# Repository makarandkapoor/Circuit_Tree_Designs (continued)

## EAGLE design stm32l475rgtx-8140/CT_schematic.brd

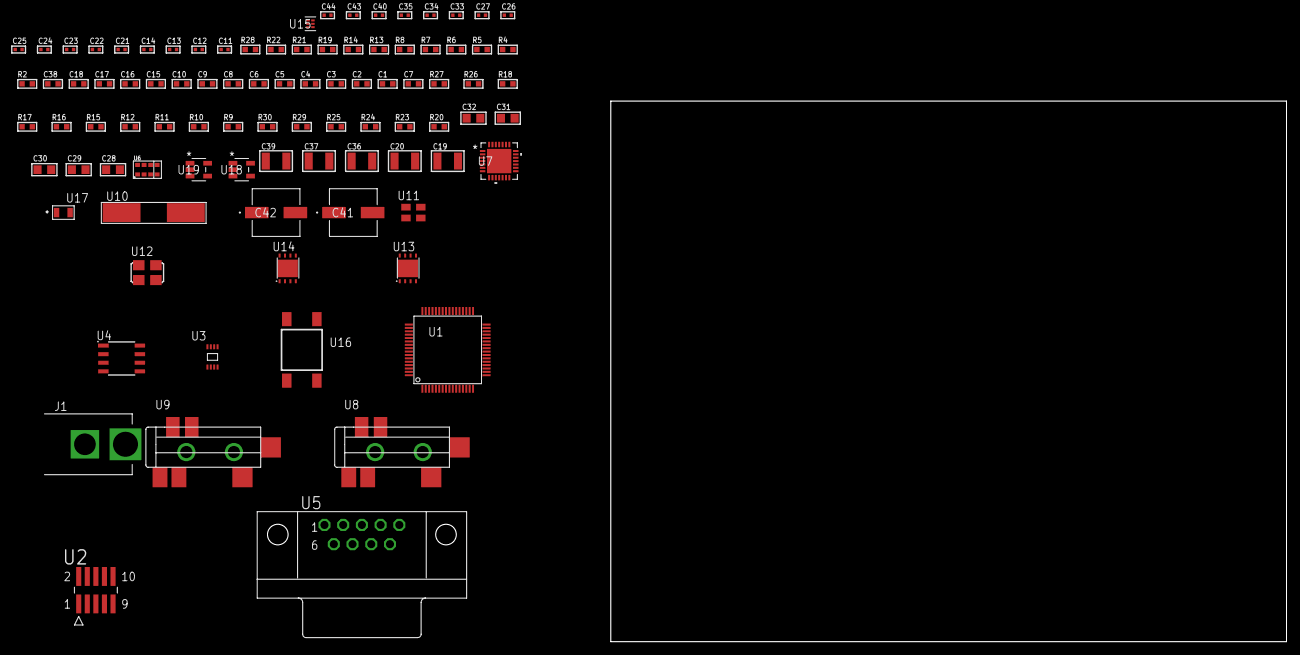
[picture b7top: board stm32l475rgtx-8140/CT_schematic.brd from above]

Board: 2 copper layers, 100.0 x 80.0 mm, 92 parts (0 on the bottom side), 42 nets, no tracks yet.

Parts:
C1, C10, C15, C16, C17, C18: 1e-06; C0603
C2, C3, C4, C5, C6, C8: 1e-07; C0603
C7: 4.7e-06; C0603
C9: 1e-08; C0603
C11, C12: 1e-11; C0402
C13, C23, C24, C25, C26, C27, C40: 1e-07; C0402
C14, C33, C34, C35, C43, C44: 1e-08; C0402
C19, C20: 2.2e-05; C1210
C21, C22: 1e-09; C0402
C28, C29, C30, C31, C32: 1e-05; C0805
C36, C37, C39: 1e-05; C1210
C38: 8e-07; R0603
C41, C42: 0.0001; EXV-9H
J1: PJ-037B; PJ-037B_PACKAGE
R2, R22: 1000.0; R0603
R4: 4700.0; R0603
R5, R6, R7, R8: 2200.0; R0603
R9, R10, R11, R12, R15, R26, R27: 10000.0; R0603
R13: 5.0; R0603
R14: 120.0; R0603
R16, R17, R18: 47000.0; R0603
R19: 680.0; R0603
R20, R23, R25: 100000.0; R0603
R21: 2231.0; R0603
R24: 300000.0; R0603
R28: 9100.0; R0603
R29: 680000.0; R0603
R30: 120000.0; R0603
U1: STM32L475RGT6; LQFP64
U2: FTSH-105-01-L-DV-K; SAMTEC_FTSH-105-01-L-DV-K
U3: 24AA16-I/MC; TDFN-8/6MM
U4: MCP2562-E/SN; SOIC-8
U5: 182-009-113R531; 182-009-MALE
U6: TMD27711; SMD-8
U7: WM8731CLSEFL; QFN-28
U8, U9: SJ-43515TS-SMT-TR
U10: ABLS-25.000MHZ-B2F-T
U11: ASEK-32.768KHz-ECST; ASEK
U12: ASFL1-12.288MHZ-EC-T; ASFL1
U13: LP3878SDX-ADJ/NOPB; WSON-8
U14: LP2951ACSDX/NOPB; WSON-8
U15: TPS3895ADRYR; SON-6
U16: 4-1437565-2; SW_4-1437565-2
U17: Q65110A2395; LGM67K-G1J2-24-Z
U18, U19: nc7sz125m5x; NC7SZ125M5X

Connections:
CLK_CRYSTAL_U1_5: C11.1, U1.5, U10.1
CLK_CRYSTAL_U1_6: C12.1, U1.6, U10.2
CLK_U1_3: U1.3, U11.3
CLK_U7_1: U7.1, U12.3
GND: C1.2, C2.2, C3.2, C4.2, C5.2, C6.2, C7.2, C8.2, C9.2, C10.2, C11.2, C12.2, C13.2, C14.2, C15.2, C16.2, C17.2, C18.2, C22.2, C23.2, C24.2, C25.2, C26.2, C27.2, C28.2, C29.2, C30.2, C31.2, C32.2, C33.2, C34.2, C35.2, C36.2, C37.2, C38.2, C39.2, C40.2, C41.2, C42.2, C43.2, C44.2, J1.2, R2.2, R9.2, R13.2, R16.2, R17.2, R18.2, R22.2, R25.2, R28.2, R30.2, U1.12, U1.18, U1.31, U1.47, U1.63, U2.3, U2.5, U3.4, U3.7, U4.2, U4.8, U5.5, U6.3, U7.4, U7.15, U7.19, U7.25, U7.26, U7.29, U8.1, U9.1, U11.2, U12.2, U13.3, U13.PAD, U14.3, U14.4, U14.PAD, U15.2, U17.C, U18.2, U18.3, U19.1, U19.3
NET_U1_7: R4.1, U1.7, U19.4
NET_U1_30: R8.1, U1.30, U3.5
NET_U1_34: R7.1, U1.34, U3.6
NET_U1_58: R5.1, U1.58, U6.2
NET_U1_59: R6.1, U1.59, U6.8
NET_U1_60: R9.1, U1.60
NET_U1_61: U16.3, U16.4
NET_U2_9: R13.1, U2.9
NET_U4_6: R14.2, U4.6
NET_U5_2: R14.2, U4.6, U5.2
NET_U5_3: R14.1, U4.7, U5.3
NET_U6_7: R15.1, U6.7
NET_U7_20: C27.1, C32.1, U7.20
NET_U8_2: C20.1, R17.1, U8.2
NET_U8_5: C19.1, R16.1, U8.5
NET_U9_5: C21.1, C22.1, R18.1, R19.1, U9.5
NET_U13_1: C35.1, U13.1
NET_U13_6: R21.2, R22.1, U13.6
NET_U13_8: R20.1, U13.8
NET_U14_5: R23.1, U14.5
NET_U14_7: R24.2, R25.1, U14.7
NET_U15_1: R27.1, R28.1, U15.1
NET_U15_3: R29.2, R30.1, U15.3
NET_U15_4: R26.1, U15.4, U18.4, U19.2
NET_U16_1: R2.1, U16.1, U16.2
PROC_CAN1_RX: U1.44, U4.4
PROC_CAN1_TX: U1.45, U4.1
PROC_SAI1_FS_A: U1.62, U7.9, U7.11
PROC_SAI1_SCK_A: U1.29, U7.7
PROC_SAI1_SD_A: U1.11, U7.8
PROC_SYS_JTCK_SWCLK: R11.1, U1.49, U2.4
PROC_SYS_JTDO_SWO: U1.55, U2.6
PROC_SYS_JTMS_SWDIO: R12.1, U1.46, U2.2
RST_OUT_U2_JTAG_RST_B: R10.1, U2.10, U18.1
VCC_S1_16V0: C36.1, C38.1, C41.1, C42.1, J1.1, R20.2, U13.4, U14.8
VCC_TIER1_3V3: C1.1, C2.1, C3.1, C4.1, C5.1, C6.1, C7.1, C8.1, C9.1, C10.1, C13.1, C14.1, C16.1, C17.1, C18.1, C23.1, C24.1, C25.1, C26.1, C28.1, C29.1, C30.1, C31.1, C33.1, C34.1, C37.1, C40.1, C43.1, C44.1, R4.2, R5.2, R6.2, R7.2, R8.2, R10.2, R11.2, R12.2, R15.2, R21.1, R26.2, R27.2, R29.1, U1.1, U1.13, U1.19, U1.32, U1.48, U1.64, U2.1, U3.8, U4.5, U6.1, U6.4, U7.3, U7.5, U7.12, U7.18, U11.4, U12.4, U13.5, U15.6, U18.5, U19.5
VCC_TIER1_5V0: C15.1, C39.1, R23.2, R24.1, U4.3, U14.1

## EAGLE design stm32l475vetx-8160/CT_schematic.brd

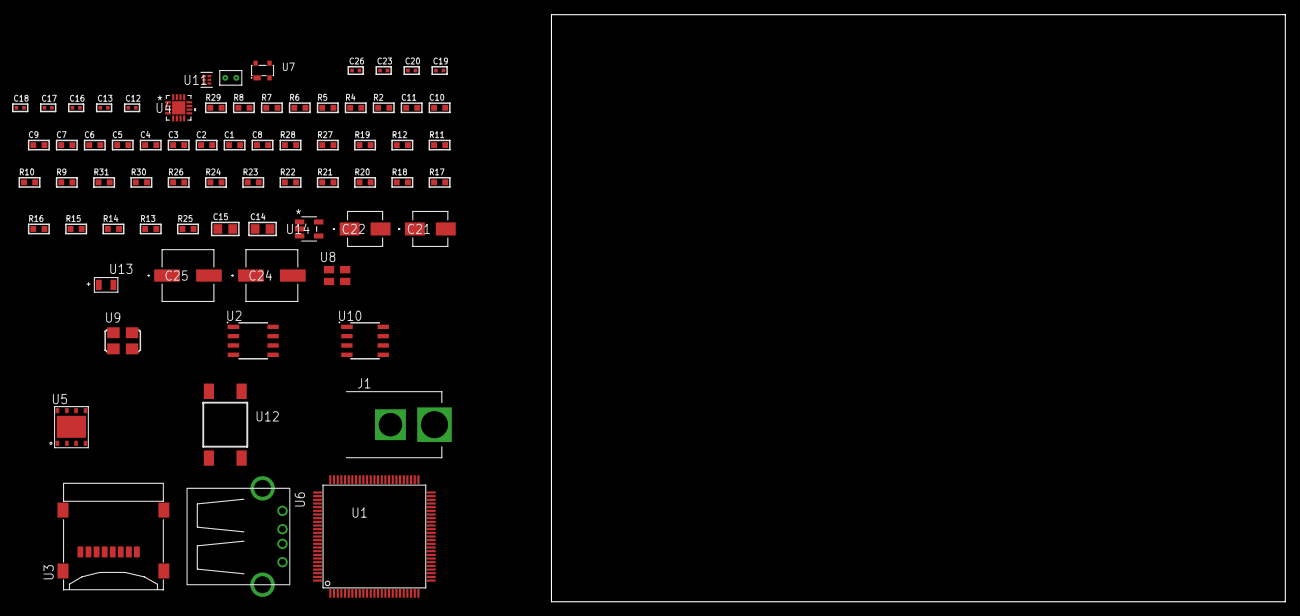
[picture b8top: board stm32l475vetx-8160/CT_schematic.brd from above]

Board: 2 copper layers, 100.0 x 80.0 mm, 71 parts (0 on the bottom side), 41 nets, no tracks yet.

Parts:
C1, C11: 1e-06; C0603
C2, C3, C4, C5, C6, C7, C9: 1e-07; C0603
C8: 4.7e-06; C0603
C10: 1e-08; C0603
C12, C19, C20, C26: 1e-08; C0402
C13, C16, C17, C18, C23: 1e-07; C0402
C14: 1e-05; C0805
C15: 4.7e-06; C0805
C21: 1e-06; EXV-9B
C22: 2.2e-06; EXV-9B
C24, C25: 0.0001; EXV-9H
J1: PJ-037B; PJ-037B_PACKAGE
R2: 1000.0; R0603
R4: 4700.0; R0603
R5, R6, R7, R8: 2200.0; R0603
R9, R10, R11, R12, R19, R27, R28: 10000.0; R0603
R13, R14, R15, R16, R17, R18, R20, R21, R22, R23, R24, R26: 100000.0; R0603
R25: 164658.62; R0603
R29: 9100.0; R0603
R30: 680000.0; R0603
R31: 120000.0; R0603
U1: STM32L475VET6; LQFP100
U2: 24AA1025T-I/SN; SOIC-8
U3: 0472192001; MOLEX_47219-2001
U4: MMA8451QT; QFN-16
U5: SST26VF032B-104I/MF; WFDN-8
U6: 61400416021; USB-A-H
U7: prtr5v0u2ax; SOT143B
U8: ASEK-32.768KHz-ECST; ASEK
U9: ASFL1-25MHZ-NCS; ASFL1
U10: LP2954AIMX/NOPB; LP2954
U11: TPS3895ADRYR; SON-6
U12: 4-1437565-2; SW_4-1437565-2
U13: Q65110A2395; LGM67K-G1J2-24-Z
U14: nc7sz125m5x; NC7SZ125M5X
U15: Dummy; DUMMY_PACKAGE_160

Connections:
CLK_U1_8: U1.8, U8.3
CLK_U1_12: U1.12, U9.3
GND: C1.2, C2.2, C3.2, C4.2, C5.2, C6.2, C7.2, C8.2, C9.2, C10.2, C11.2, C12.2, C13.2, C14.2, C15.2, C16.2, C17.2, C18.2, C19.2, C20.2, C21.2, C22.2, C23.2, C24.2, C25.2, C26.2, J1.2, R2.2, R9.2, R11.2, R19.2, R26.2, R29.2, R31.2, U1.10, U1.19, U1.20, U1.27, U1.49, U1.74, U1.99, U2.4, U2.7, U3.6, U3.G1, U3.G2, U3.G3, U3.G4, U4.5, U4.10, U4.12, U4.17, U5.4, U5.9, U6.4, U6.5, U6.6, U7.1, U8.2, U9.2, U10.4, U11.2, U13.C, U14.1, U14.3, U15.1
NET_U1_14: R4.1, U1.14, U14.4
NET_U1_22: U1.21, U1.22
NET_U1_47: R7.1, U1.47, U2.6
NET_U1_48: R8.1, U1.48, U2.5
NET_U1_92: R5.1, U1.92, U4.4
NET_U1_93: R6.1, U1.93, U4.6
NET_U1_94: R9.1, U1.94
NET_U1_98: U12.3, U12.4
NET_U2_1: R11.1, U2.1
NET_U2_2: R12.1, U2.2
NET_U2_3: R10.1, U2.3
NET_U4_2: C17.1, U4.2
NET_U4_7: R19.1, U4.7
NET_U10_3: R24.1, U10.3
NET_U10_5: R23.1, U10.5
NET_U10_7: R25.2, R26.1, U10.7
NET_U11_1: R28.1, R29.1, U11.1
NET_U11_3: R30.2, R31.1, U11.3
NET_U11_4: R27.1, U11.4, U14.2
NET_U12_1: R2.1, U12.1, U12.2
PROC_DAC1_OUT2: U1.30, U15.2
PROC_QUADSPI_BK1_IO0: U1.36, U5.5
PROC_QUADSPI_BK1_IO1: U1.35, U5.2
PROC_QUADSPI_BK1_IO2: R21.1, U1.32, U5.3
PROC_QUADSPI_BK1_IO3: R22.1, U1.31, U5.7
PROC_QUADSPI_CLK: U1.41, U5.6
PROC_QUADSPI_NCS: R20.1, U1.42, U5.1
PROC_SDMMC1_CK: R14.1, U1.80, U3.5
PROC_SDMMC1_CMD: R13.1, U1.83, U3.3
PROC_SDMMC1_D0: R15.1, U1.65, U3.7
PROC_SDMMC1_D1: R16.1, U1.66, U3.8
PROC_SDMMC1_D2: R17.1, U1.78, U3.1
PROC_SDMMC1_D3: R18.1, U1.79, U3.2
PROC_USB_OTG_FS_DM: U6.2, U7.3
PROC_USB_OTG_FS_DP: U6.3, U7.2
PROC_USB_OTG_FS_VBUS: U6.1, U7.4
VCC_S1_16V8: C21.1, C24.1, C25.1, J1.1, R24.2, U10.8
VCC_TIER1_3V3: C1.1, C2.1, C3.1, C4.1, C5.1, C6.1, C7.1, C8.1, C9.1, C10.1, C11.1, C12.1, C13.1, C14.1, C15.1, C16.1, C18.1, C19.1, C20.1, C22.1, C23.1, C26.1, R4.2, R5.2, R6.2, R7.2, R8.2, R10.2, R12.2, R13.2, R14.2, R15.2, R16.2, R17.2, R18.2, R20.2, R21.2, R22.2, R23.2, R25.1, R27.2, R28.2, R30.1, U1.6, U1.11, U1.22, U1.28, U1.50, U1.73, U1.75, U1.100, U2.8, U3.4, U4.1, U4.14, U5.8, U8.4, U9.4, U10.1, U11.6, U14.5
